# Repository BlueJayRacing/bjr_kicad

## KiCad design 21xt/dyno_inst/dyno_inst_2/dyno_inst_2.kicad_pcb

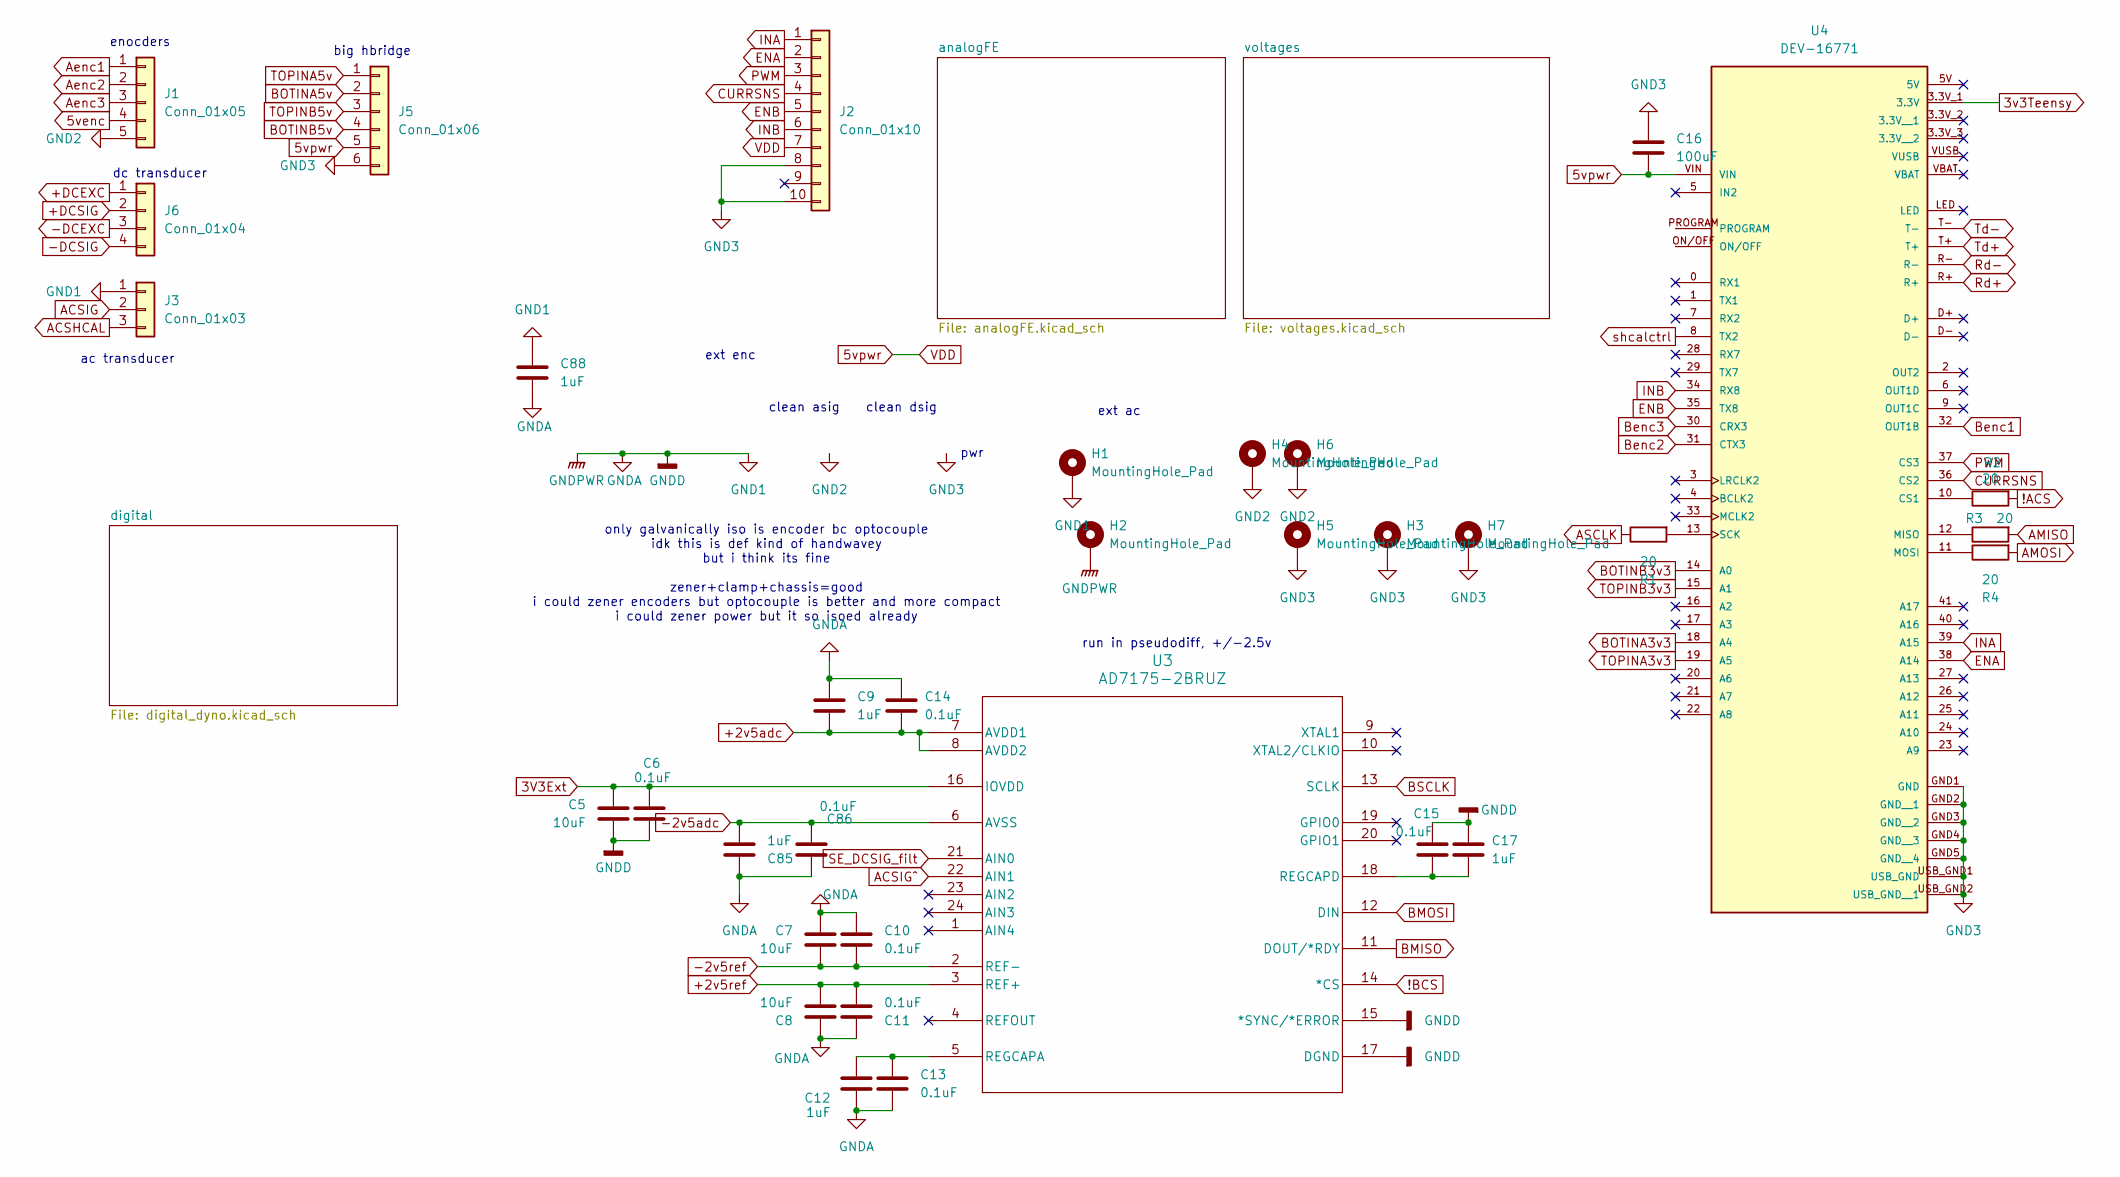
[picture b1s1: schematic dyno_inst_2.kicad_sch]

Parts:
C5, C7, C8: 10uF; C_0402_1005Metric
C6, C10, C11, C13, C14, C15, C86: 0.1uF; C_0402_1005Metric
C9, C12, C17, C85: 1uF; C_0402_1005Metric
C16: 100uF; C_0603_1608Metric
C88: 1uF; C_0603_1608Metric
H1, H2, H3, H4, H5, H6, H7: MountingHole_Pad; MountingHole_3mm_Pad
J1: Conn_01x05; PinHeader_1x05_P2.54mm_Vertical
J2: Conn_01x10; PinHeader_1x10_P2.54mm_Vertical
J3: Conn_01x03; CONN_T4041017041-000_TEC
J5: Conn_01x06; PinHeader_1x06_P2.54mm_Vertical
J6: Conn_01x04; CONN_T4041017041-000_TEC
R1, R2, R3, R4: 20; R_0402_1005Metric
U3: AD7175-2BRUZ; RU_24_ADI
U4: DEV-16771; MODULE_DEV-16771; PARTREV 4.1

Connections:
3V3Ext: C5.1, C6.1, U3.16 (IOVDD)
3v3Teensy: U4.3.3V_1 (3.3V); also elsewhere on the board
5venc: J1.4; also elsewhere on the board
5vpwr: C16.2, J2.7, J5.5, U4.VIN; also elsewhere on the board
!ACS: R2.2; also elsewhere on the board
!BCS: U3.14 (*CS); also elsewhere on the board
+2v5adc: C9.2, C14.2, U3.7 (AVDD1), U3.8 (AVDD2); also elsewhere on the board
+2v5ref: C8.2, C11.2, U3.3 (REF+); also elsewhere on the board
+5vexc: J6.1; also elsewhere on the board
+DCSIG: J6.2; also elsewhere on the board
-2v5adc: C85.2, C86.2, U3.6 (AVSS); also elsewhere on the board
-2v5ref: C7.2, C10.2, U3.2 (REF-); also elsewhere on the board
-5vexc: J6.3; also elsewhere on the board
-DCSIG: J6.4; also elsewhere on the board
ACSHCAL: J3.3; also elsewhere on the board
ACSIG: J3.2; also elsewhere on the board
ACSIG^: U3.22 (AIN1); also elsewhere on the board
AMISO: R3.2; also elsewhere on the board
AMOSI: R4.2; also elsewhere on the board
ASCLK: R1.1; also elsewhere on the board
Aenc1: J1.1; also elsewhere on the board
Aenc2: J1.2; also elsewhere on the board
Aenc3: J1.3; also elsewhere on the board
BMISO: U3.11 (DOUT/*RDY); also elsewhere on the board
BMOSI: U3.12 (DIN); also elsewhere on the board
BOTINA3v3: U4.18 (A4); also elsewhere on the board
BOTINA5v: J5.2; also elsewhere on the board
BOTINB3v3: U4.14 (A0); also elsewhere on the board
BOTINB5v: J5.4; also elsewhere on the board
BSCLK: U3.13 (SCLK); also elsewhere on the board
Benc1: U4.32 (OUT1B); also elsewhere on the board
Benc2: U4.31 (CTX3); also elsewhere on the board
Benc3: U4.30 (CRX3); also elsewhere on the board
CURRSNS: J2.4, U4.36 (CS2)
ENA: J2.2, U4.38 (A14)
ENB: J2.5, U4.35 (TX8)
GND1: C5.2, C6.2, C7.1, C8.1, C9.1, C10.1, C11.1, C12.2, C13.2, C14.1, C15.1, C17.1, C85.1, C86.1, C88.1, C88.2, H1.1, H2.1, J3.1, U3.15 (*SYNC/*ERROR), U3.17 (DGND); also elsewhere on the board
GND2: H4.1, H6.1, J1.5; also elsewhere on the board
GND3: C16.1, H3.1, H5.1, H7.1, J2.8, J2.10, J5.6, U4.GND1 (GND), U4.GND2 (GND__1), U4.GND3 (GND__2), U4.GND4 (GND__3), U4.GND5 (GND__4), U4.USB_GND1 (USB_GND), U4.USB_GND2 (USB_GND__1); also elsewhere on the board
INA: J2.1, U4.39 (A15)
INB: J2.6, U4.34 (RX8)
unnamed: C12.1, C13.1, U3.5 (REGCAPA)
unnamed: C15.2, C17.2, U3.18 (REGCAPD)
unnamed: R2.1, U4.10 (CS1)
unnamed: R3.1, U4.12 (MISO)
unnamed: R4.1, U4.11 (MOSI)
unnamed: R1.2, U4.13 (SCK)
PWM: J2.3, U4.37 (CS3)
Rd+: U4.R+; also elsewhere on the board
Rd-: U4.R-; also elsewhere on the board
SE_DCSIG_filt: U3.21 (AIN0); also elsewhere on the board
TOPINA3v3: U4.19 (A5); also elsewhere on the board
TOPINA5v: J5.1; also elsewhere on the board
TOPINB3v3: U4.15 (A1); also elsewhere on the board
TOPINB5v: J5.3; also elsewhere on the board
Td+: U4.T+; also elsewhere on the board
Td-: U4.T-; also elsewhere on the board
shcalctrl: U4.8 (TX2); also elsewhere on the board

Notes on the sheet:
dc transducer
clean dsig
big hbridge
pwr
ext enc
only galvanically iso is encoder bc optocouple idk this is def kind of handwavey but i think its fine zener+clamp+chassis=good i could zener encoders but optocouple is better and more compact i could zener power but it so isoed already
run in pseudodiff, +/-2.5v
ext ac
clean asig
enocders
ac transducer

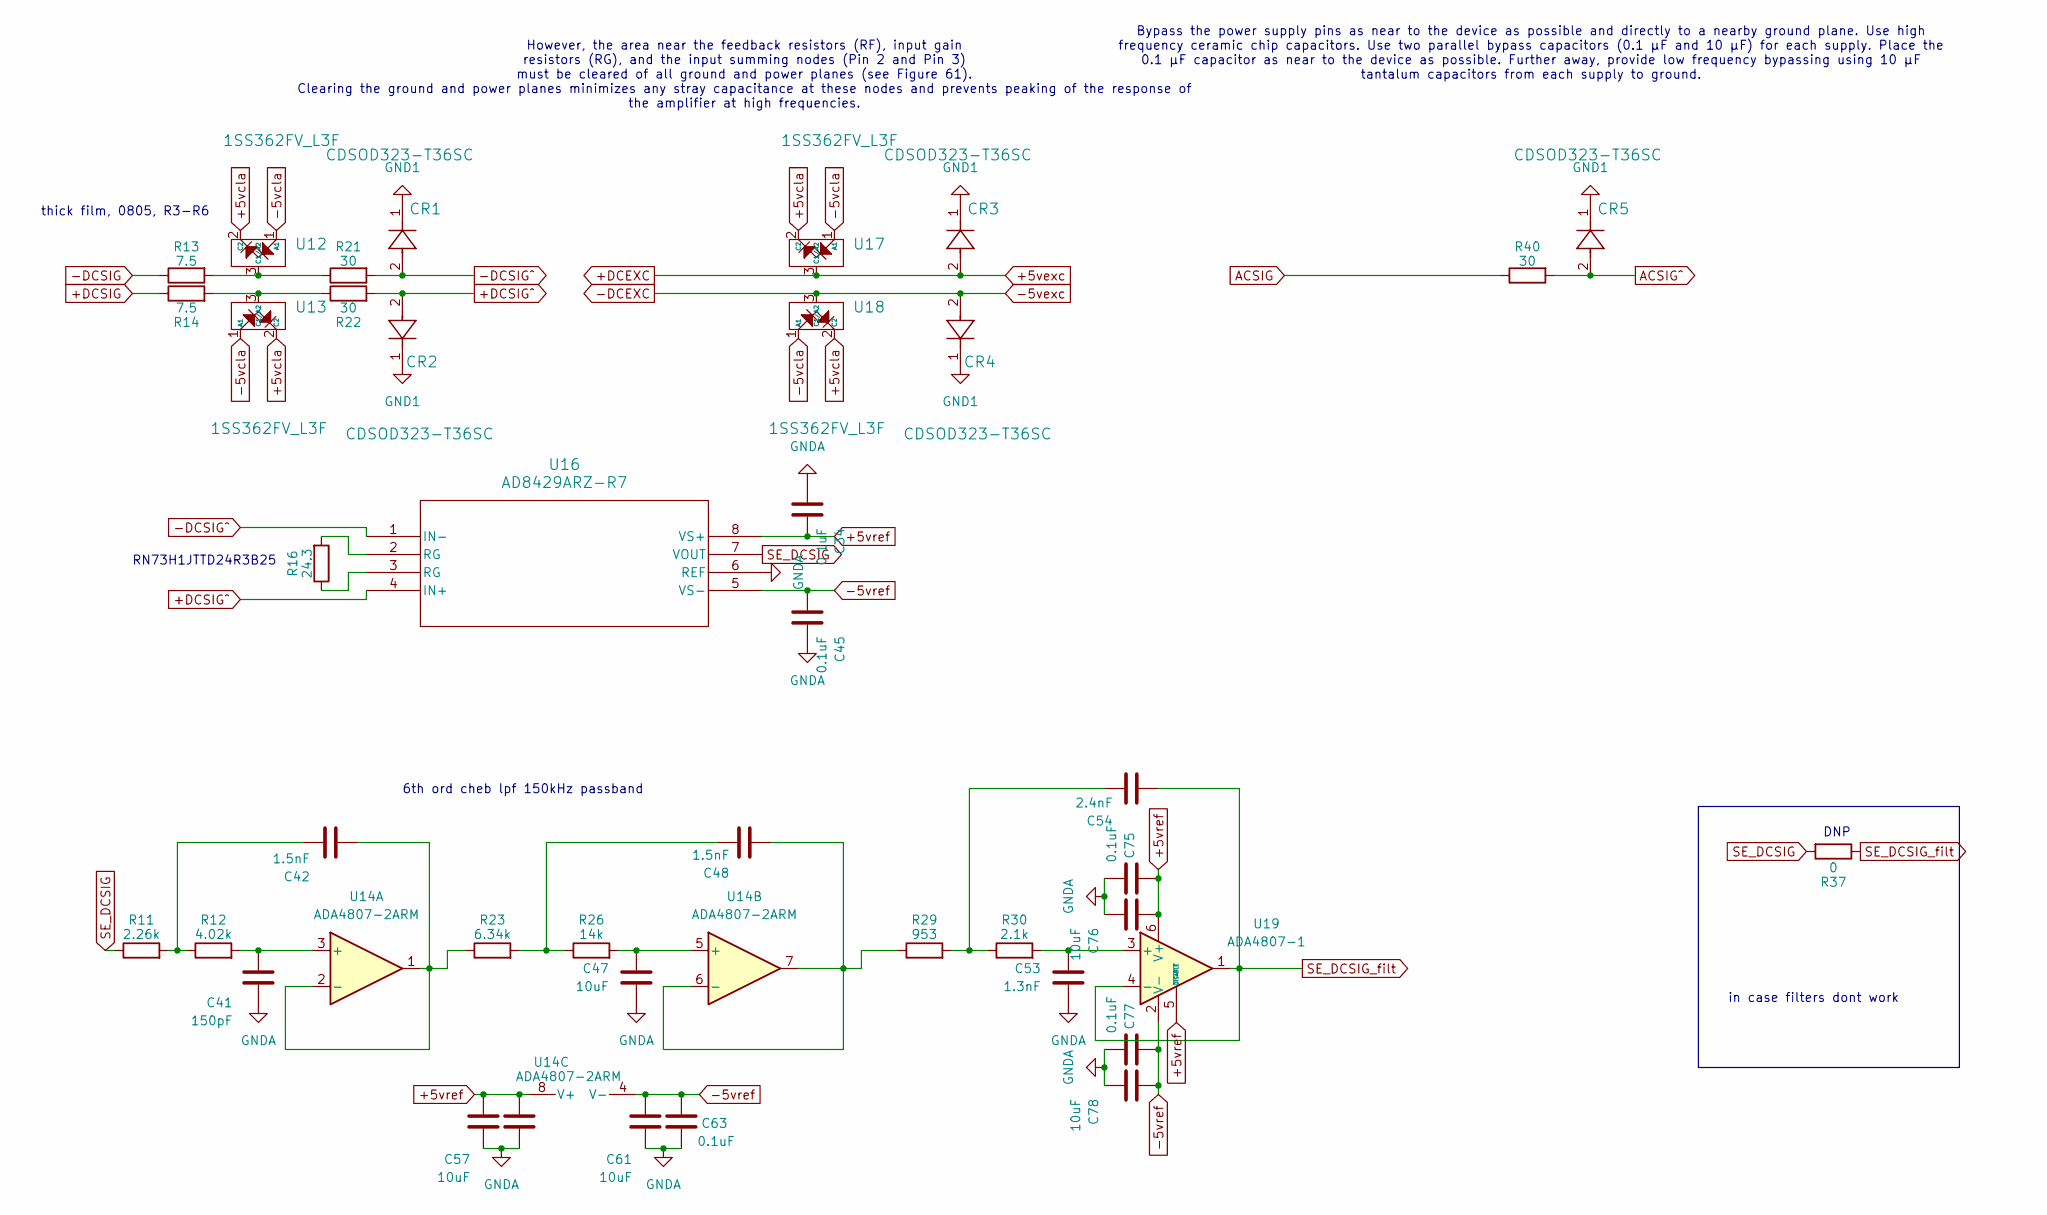
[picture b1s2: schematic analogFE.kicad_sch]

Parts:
C34, C45, C58, C63, C75, C77: 0.1uF; C_0402_1005Metric
C41: 150pF; C_0402_1005Metric
C42, C48: 1.5nF; C_0402_1005Metric
C47, C57, C61, C76, C78: 10uF; C_0402_1005Metric
C53: 1.3nF; C_0402_1005Metric
C54: 2.4nF; C_0402_1005Metric
CR1, CR2, CR3, CR4, CR5: CDSOD323-T36SC; DIODE_CDSOD323-T36SC_BRN
R11: 2.26k; R_0402_1005Metric
R12: 4.02k; R_0402_1005Metric
R13, R14: 7.5; R_0805_2012Metric
R16: 24.3; R_0805_2012Metric
R21, R22, R40: 30; R_0805_2012Metric
R23: 6.34k; R_0402_1005Metric
R26: 14k; R_0402_1005Metric
R29: 953; R_0402_1005Metric
R30: 2.1k; R_0402_1005Metric
R37: 0; R_0402_1005Metric
U12, U13, U17, U18: 1SS362FV_L3F; SOT-723
U14: ADA4807-2ARM; MSOP-8_3x3mm_P0.65mm
U16: AD8429ARZ-R7; R_8_ADI
U19: ADA4807-1; KS-6_ADI

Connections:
+5vcla: U12.2 (C2), U13.2 (C2), U17.2 (C2), U18.2 (C2); also elsewhere on the board
+5vexc: CR3.2, U17.3 (C1/A2); also elsewhere on the board
+5vref: C34.1, C57.1, C58.1, C75.1, C76.1, U14.8 (V+), U16.8 (VS+), U19.5 (~DISABLE), U19.6 (V+); also elsewhere on the board
+DCSIG: R14.1; also elsewhere on the board
+DCSIG^: CR2.2, R22.2, U16.4 (IN+)
-5vcla: U12.1 (A1), U13.1 (A1), U17.1 (A1), U18.1 (A1); also elsewhere on the board
-5vexc: CR4.2, U18.3 (C1/A2); also elsewhere on the board
-5vref: C45.2, C61.1, C63.1, C77.1, C78.1, U14.4 (V-), U16.5 (VS-), U19.2 (V-); also elsewhere on the board
-DCSIG: R13.1; also elsewhere on the board
-DCSIG^: CR1.2, R21.2, U16.1 (IN-)
ACSIG: R40.1; also elsewhere on the board
ACSIG^: CR5.2, R40.2; also elsewhere on the board
GND1: C34.2, C41.2, C45.1, C47.2, C53.2, C57.2, C58.2, C61.2, C63.2, C75.2, C76.2, C77.2, C78.2, CR1.1, CR2.1, CR3.1, CR4.1, CR5.1, U16.6 (REF); also elsewhere on the board
unnamed: C42.1, R11.2, R12.1
unnamed: C48.1, R23.2, R26.1
unnamed: C54.1, R29.2, R30.1
unnamed: R16.1, U16.3 (RG)
unnamed: R16.2, U16.2 (RG)
unnamed: R13.2, R21.1, U12.3 (C1/A2)
unnamed: R14.2, R22.1, U13.3 (C1/A2)
unnamed: C41.1, R12.2, U14.3 (+)
unnamed: C42.2, R23.1, U14.1, U14.2 (-)
unnamed: C47.1, R26.2, U14.5 (+)
unnamed: C48.2, R29.1, U14.6 (-), U14.7
unnamed: C53.1, R30.2, U19.3 (+)
SE_DCSIG: R11.1, R37.2, U16.7 (VOUT)
SE_DCSIG_filt: C54.2, R37.1, U19.1, U19.4 (-); also elsewhere on the board

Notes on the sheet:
in case filters dont work
RN73H1JTTD24R3B25
DNP
6th ord cheb lpf 150kHz passband
However, the area near the feedback resistors (RF), input gain resistors (RG), and the input summing nodes (Pin 2 and Pin 3) must be cleared of all ground and power planes (see Figure 61). Clearing the ground and power planes minimizes any stray capacitance at these nodes and prevents peaking of th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
Bypass the power supply pins as near to the device as possible and directly to a nearby ground plane. Use high frequency ceramic chip capacitors. Use two parallel bypass capacitors (0.1 µF and 10 µF) for each supply. Place the 0.1 µF capacitor as near to the device as possible. Further away, provid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
thick film, 0805, R3-R6

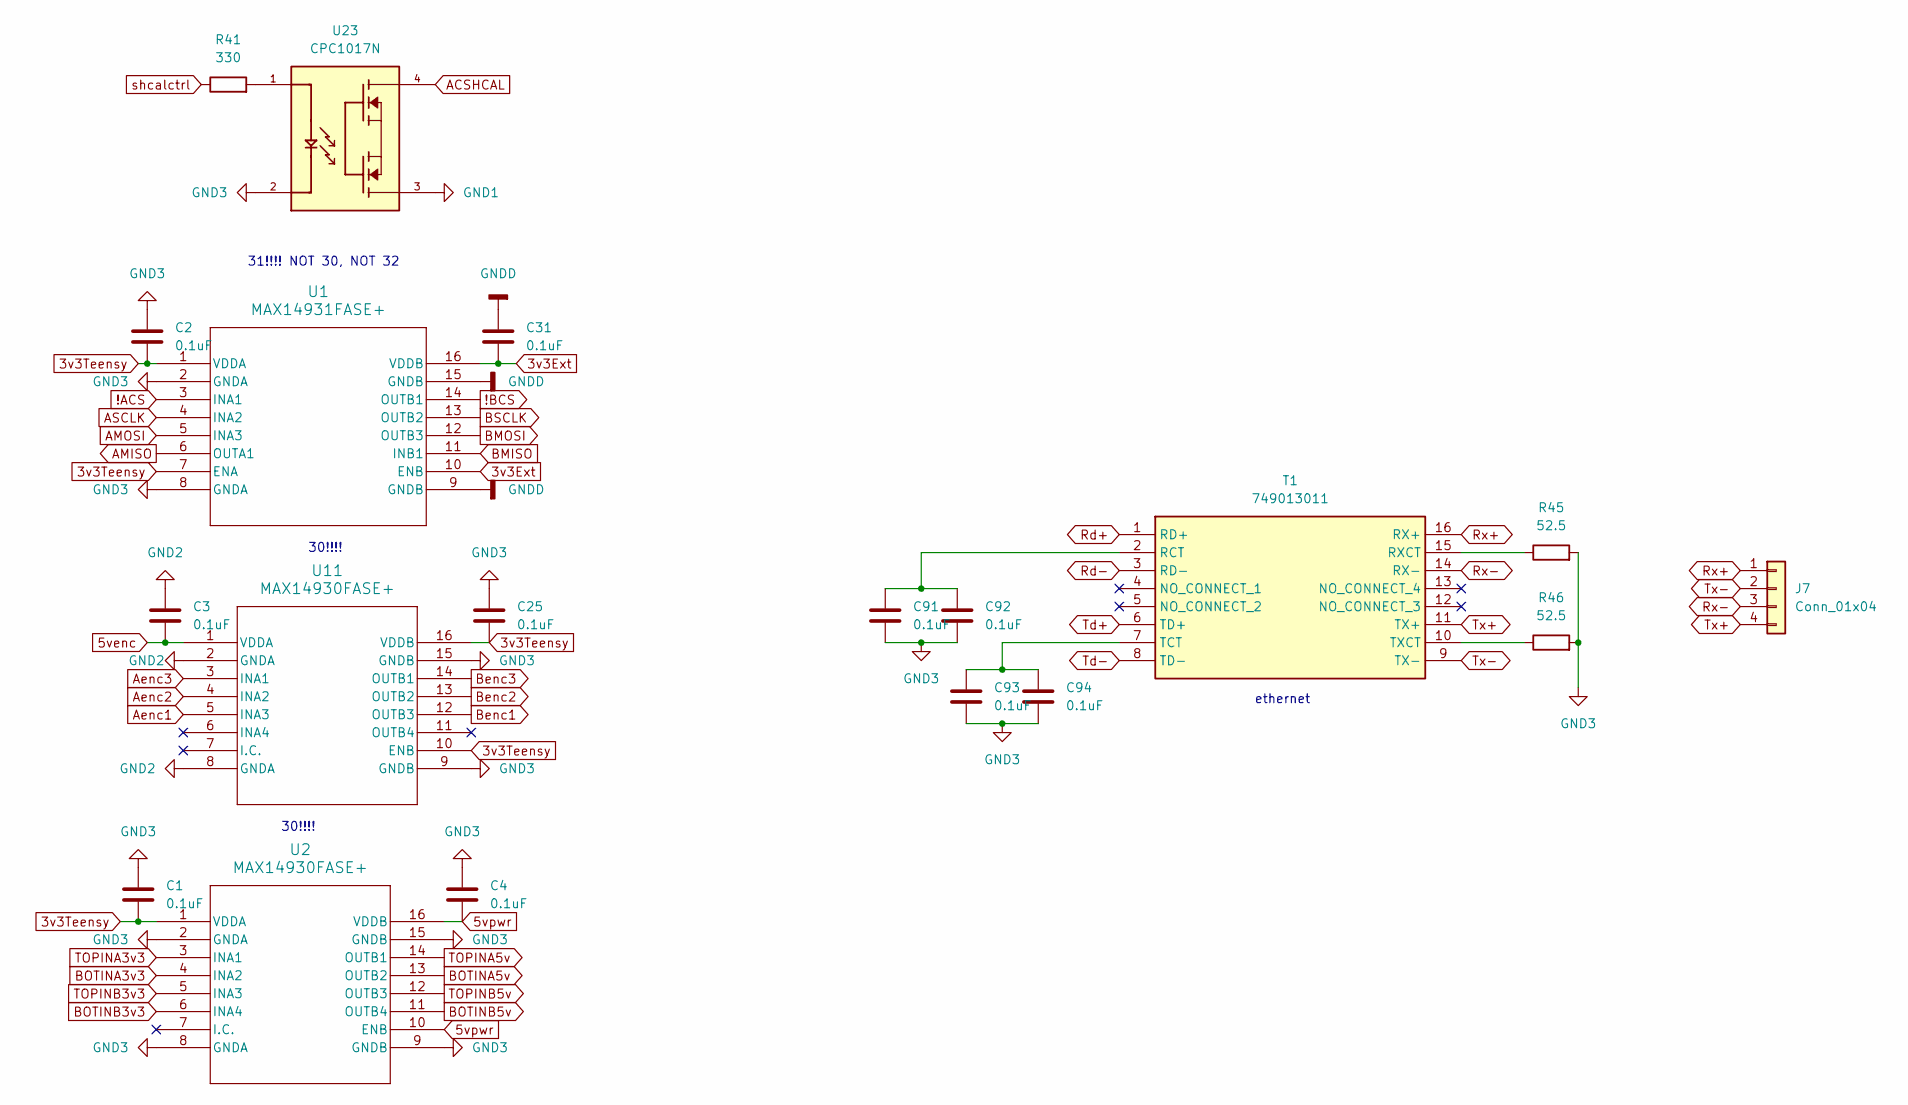
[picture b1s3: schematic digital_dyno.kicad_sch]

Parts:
C1, C2, C3, C4, C25, C31, C91, C92, C93, C94: 0.1uF; C_0402_1005Metric
J7: Conn_01x04; CONN_T4041017041-000_TEC
R41: 330; R_0402_1005Metric
R45, R46: 52.5; R_0402_1005Metric
T1: 749013011; Mouser Part Number 710-749013011
U1: MAX14931FASE+; 21-0041_S16&plus_1_MXM_1
U2, U11: MAX14930FASE+; 21-0041_S16&plus_1_MXM
U23: CPC1017N; SOIC254P610X218-4N

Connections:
3v3Ext: C31.2, U1.10 (ENB), U1.16 (VDDB); also elsewhere on the board
3v3Teensy: C1.2, C2.2, C25.2, U1.1 (VDDA), U1.7 (ENA), U2.1 (VDDA), U11.10 (ENB), U11.16 (VDDB); also elsewhere on the board
5venc: C3.2, U11.1 (VDDA); also elsewhere on the board
5vpwr: C4.2, U2.10 (ENB), U2.16 (VDDB); also elsewhere on the board
!ACS: U1.3 (INA1); also elsewhere on the board
!BCS: U1.14 (OUTB1); also elsewhere on the board
ACSHCAL: U23.4; also elsewhere on the board
AMISO: U1.6 (OUTA1); also elsewhere on the board
AMOSI: U1.5 (INA3); also elsewhere on the board
ASCLK: U1.4 (INA2); also elsewhere on the board
Aenc1: U11.5 (INA3); also elsewhere on the board
Aenc2: U11.4 (INA2); also elsewhere on the board
Aenc3: U11.3 (INA1); also elsewhere on the board
BMISO: U1.11 (INB1); also elsewhere on the board
BMOSI: U1.12 (OUTB3); also elsewhere on the board
BOTINA3v3: U2.4 (INA2); also elsewhere on the board
BOTINA5v: U2.13 (OUTB2); also elsewhere on the board
BOTINB3v3: U2.6 (INA4); also elsewhere on the board
BOTINB5v: U2.11 (OUTB4); also elsewhere on the board
BSCLK: U1.13 (OUTB2); also elsewhere on the board
Benc1: U11.12 (OUTB3); also elsewhere on the board
Benc2: U11.13 (OUTB2); also elsewhere on the board
Benc3: U11.14 (OUTB1); also elsewhere on the board
GND1: C31.1, U1.9 (GNDB), U1.15 (GNDB), U23.3; also elsewhere on the board
GND2: C3.1, U11.2 (GNDA), U11.8 (GNDA); also elsewhere on the board
GND3: C1.1, C2.1, C4.1, C25.1, C91.2, C92.2, C93.2, C94.2, R45.2, R46.2, U1.2 (GNDA), U1.8 (GNDA), U2.2 (GNDA), U2.8 (GNDA), U2.9 (GNDB), U2.15 (GNDB), U11.9 (GNDB), U11.15 (GNDB), U23.2; also elsewhere on the board
unnamed: R41.2, U23.1
unnamed: C91.1, C92.1, T1.2 (RCT)
unnamed: R45.1, T1.15 (RXCT)
unnamed: C93.1, C94.1, T1.7 (TCT)
unnamed: R46.1, T1.10 (TXCT)
Rd+: T1.1 (RD+); also elsewhere on the board
Rd-: T1.3 (RD-); also elsewhere on the board
Rx+: J7.1, T1.16 (RX+)
Rx-: J7.3, T1.14 (RX-)
TOPINA3v3: U2.3 (INA1); also elsewhere on the board
TOPINA5v: U2.14 (OUTB1); also elsewhere on the board
TOPINB3v3: U2.5 (INA3); also elsewhere on the board
TOPINB5v: U2.12 (OUTB3); also elsewhere on the board
Td+: T1.6 (TD+); also elsewhere on the board
Td-: T1.8 (TD-); also elsewhere on the board
Tx+: J7.4, T1.11 (TX+)
Tx-: J7.2, T1.9 (TX-)
shcalctrl: R41.1; also elsewhere on the board

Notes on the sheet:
31!!!! NOT 30, NOT 32
30!!!!
ethernet

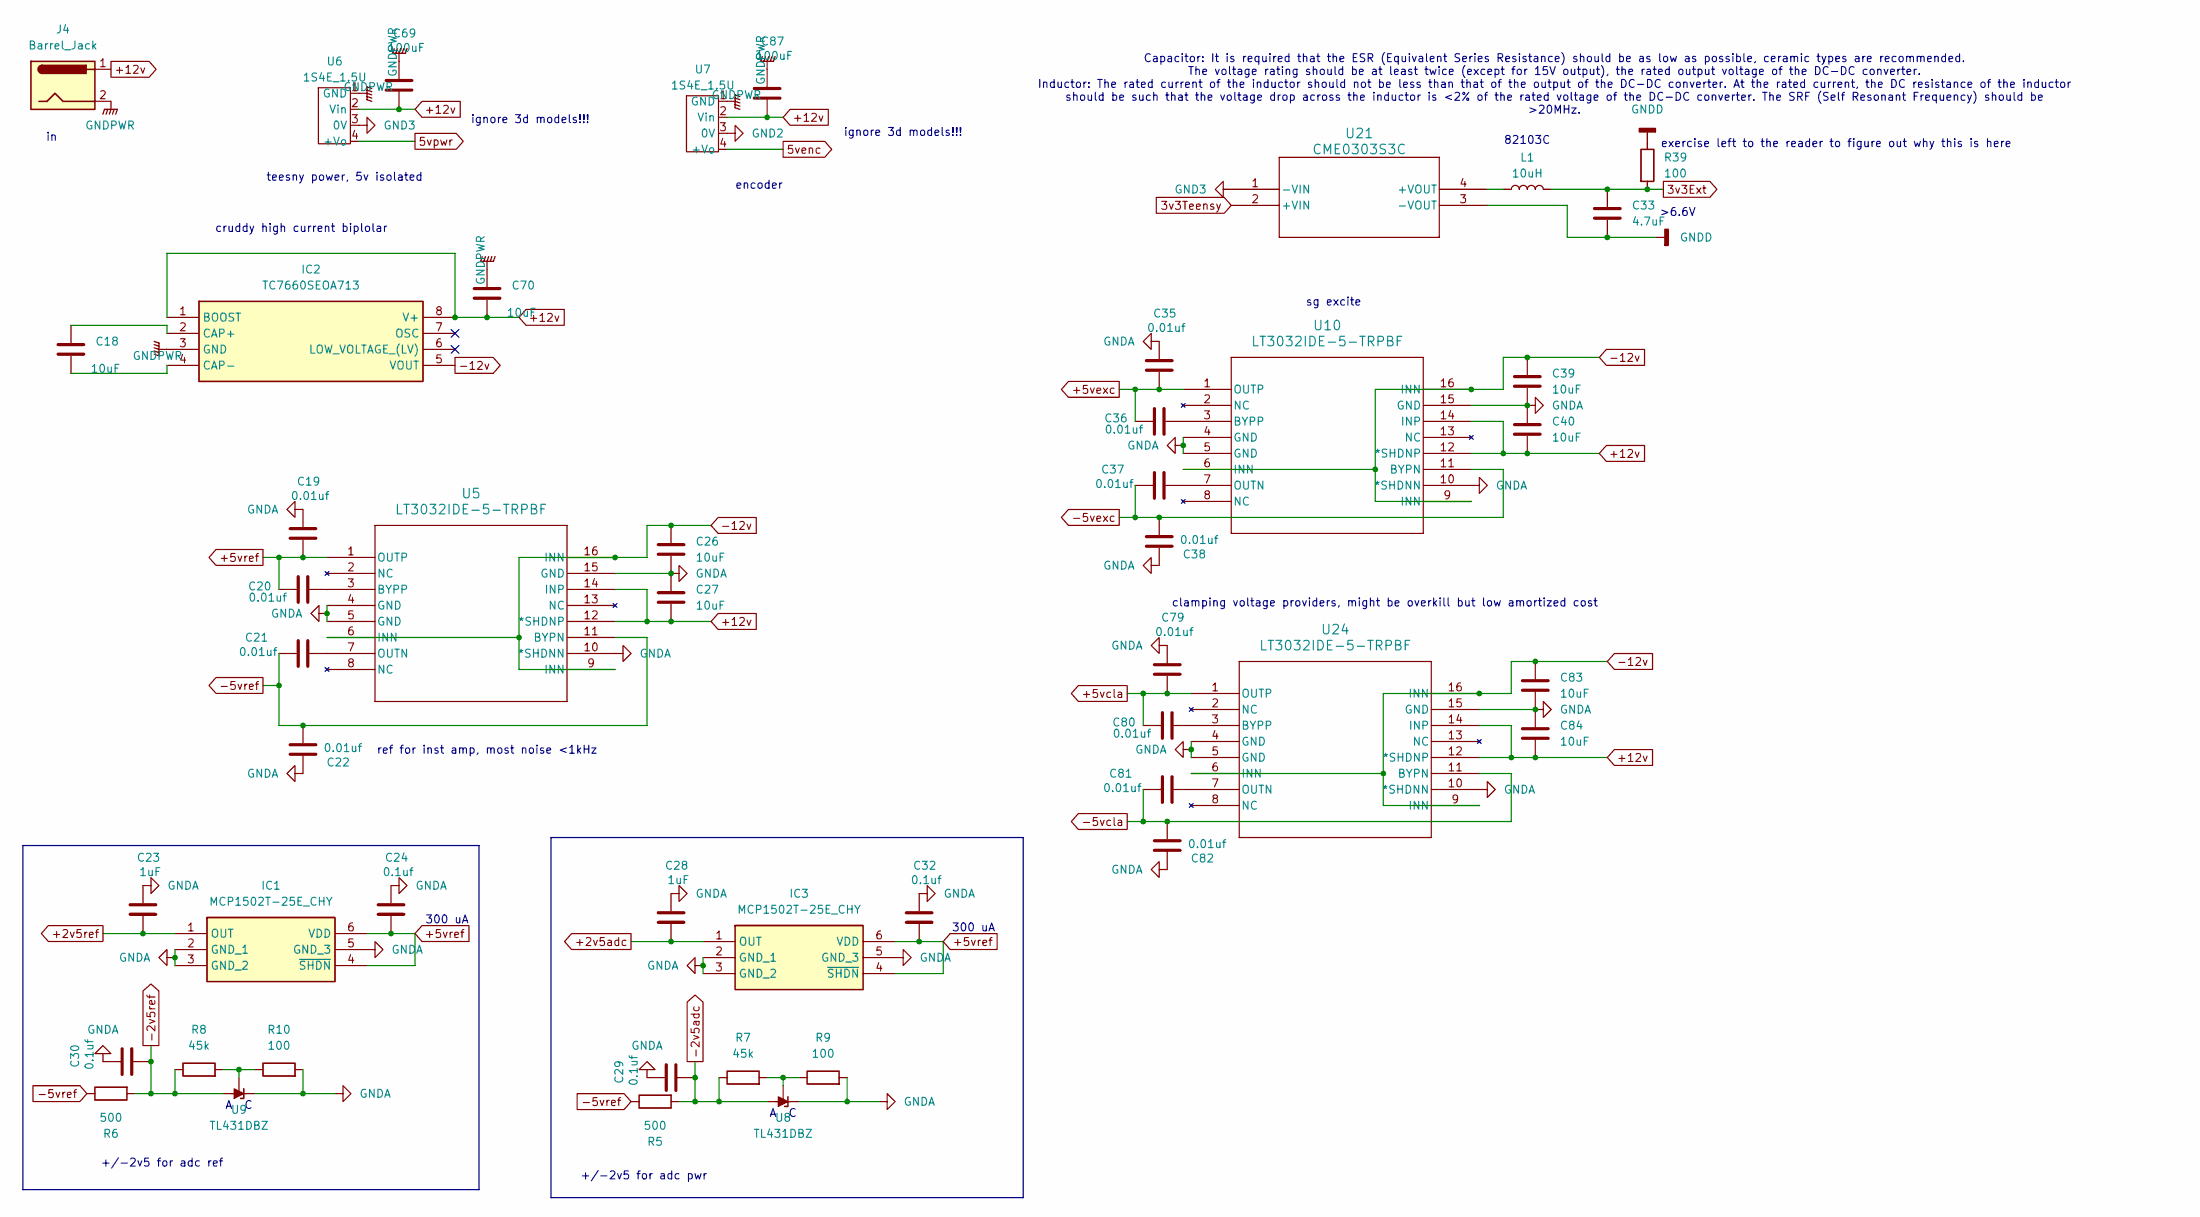
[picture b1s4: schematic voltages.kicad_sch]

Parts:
C18, C70: 10uF; C_0603_1608Metric
C19, C20, C21, C22, C35, C36, C37, C38, C79, C80, C81, C82: 0.01uf; C_0402_1005Metric
C23, C28: 1uF; C_0402_1005Metric
C24, C29, C30, C32: 0.1uf; C_0402_1005Metric
C26, C27, C39, C40, C83, C84: 10uF; C_0402_1005Metric
C33: 4.7uF; C_0402_1005Metric
C69, C87: 100uF; C_0805_2012Metric
IC1, IC3: MCP1502T-25E_CHY; SOT95P280X145-6N; Mouser Part Number 579-MCP1502T-50E/CHY
IC2: TC7660SEOA713; SOIC127P600X175-8N; Mouser Part Number 579-TC7660SEOA713
J4: Barrel_Jack; CUI_PJ-037A
L1: 10uH; L_1210_3225Metric
R5, R6: 500; R_0402_1005Metric
R7, R8: 45k; R_0402_1005Metric
R9, R10, R39: 100; R_0402_1005Metric
U5, U10, U24: LT3032IDE-5-TRPBF; DFN14_DE14MA_ADI
U6, U7: 1S4E_1.5U; PinHeader_1x04_P2.54mm_Vertical
U8, U9: TL431DBZ; SOT-23
U21: CME0303S3C; SIP4_CME0303_MUR

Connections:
3v3Ext: C33.1, L1.2, R39.2; also elsewhere on the board
3v3Teensy: U21.2 (+VIN); also elsewhere on the board
5venc: U7.4 (+Vo); also elsewhere on the board
5vpwr: U6.4 (+Vo); also elsewhere on the board
+2v5adc: C28.2, IC3.1 (OUT); also elsewhere on the board
+2v5ref: C23.2, IC1.1 (OUT); also elsewhere on the board
+5vcla: C79.2, C80.1, U24.1 (OUTP); also elsewhere on the board
+5vexc: C35.2, C36.1, U10.1 (OUTP); also elsewhere on the board
+5vref: C19.2, C20.1, C24.2, C32.2, IC1.4 (~SHDN), IC1.6 (VDD), IC3.4 (~SHDN), IC3.6 (VDD), U5.1 (OUTP); also elsewhere on the board
+12v: C27.2, C40.2, C69.2, C70.2, C84.2, C87.2, IC2.1 (BOOST), IC2.8 (V+), J4.1, U5.12 (*SHDNP), U5.14 (INP), U6.2 (Vin), U7.2 (Vin), U10.12 (*SHDNP), U10.14 (INP), U24.12 (*SHDNP), U24.14 (INP)
-2v5adc: C29.2, R5.2, R7.1, U8.3 (A); also elsewhere on the board
-2v5ref: C30.2, R6.2, R8.1, U9.3 (A); also elsewhere on the board
-5vcla: C81.1, C82.2, U24.11 (BYPN); also elsewhere on the board
-5vexc: C37.1, C38.2, U10.11 (BYPN); also elsewhere on the board
-5vref: C21.1, C22.2, R5.1, R6.1, U5.11 (BYPN); also elsewhere on the board
-12v: C26.1, C39.1, C83.1, IC2.5 (VOUT), U5.6 (INN), U5.9 (INN), U5.16 (INN), U10.6 (INN), U10.9 (INN), U10.16 (INN), U24.6 (INN), U24.9 (INN), U24.16 (INN)
GND1: C19.1, C22.1, C23.1, C24.1, C26.2, C27.1, C28.1, C29.1, C30.1, C32.1, C33.2, C35.1, C38.1, C39.2, C40.1, C69.1, C70.1, C79.1, C82.1, C83.2, C84.1, C87.1, IC1.2 (GND_1), IC1.3 (GND_2), IC1.5 (GND_3), IC2.3 (GND), IC3.2 (GND_1), IC3.3 (GND_2), IC3.5 (GND_3), J4.2, R9.2, R10.2, R39.1, U5.4 (GND), U5.5 (GND), U5.10 (*SHDNN), U5.15 (GND), U6.1 (GND), U7.1 (GND), U8.1 (K), U9.1 (K), U10.4 (GND), U10.5 (GND), U10.10 (*SHDNN), U10.15 (GND), U21.3 (-VOUT), U24.4 (GND), U24.5 (GND), U24.10 (*SHDNN), U24.15 (GND); also elsewhere on the board
GND2: U7.3 (0V); also elsewhere on the board
GND3: U6.3 (0V), U21.1 (-VIN); also elsewhere on the board
unnamed: C18.1, IC2.2 (CAP+)
unnamed: C18.2, IC2.4 (CAP-)
unnamed: C20.2, U5.3 (BYPP)
unnamed: C21.2, U5.7 (OUTN)
unnamed: R7.2, R9.1, U8.2 (REF)
unnamed: R8.2, R10.1, U9.2 (REF)
unnamed: C36.2, U10.3 (BYPP)
unnamed: C37.2, U10.7 (OUTN)
unnamed: L1.1, U21.4 (+VOUT)
unnamed: C80.2, U24.3 (BYPP)
unnamed: C81.2, U24.7 (OUTN)

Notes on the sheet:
cruddy high current biplolar
clamping voltage providers, might be overkill but low amortized cost
exercise left to the reader to figure out why this is here
encoder
Capacitor: It is required that the ESR (Equivalent Series Resistance) should be as low as possible, ceramic types are recommended. The voltage rating should be at least twice (except for 15V output), the rated output voltage of the DC-DC converter. Inductor: The rated current of the inductor should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
ignore 3d models!!!
+/-2v5 for adc pwr
300 uA
+/-2v5 for adc ref
teesny power, 5v isolated
A C
>6.6V
sg excite
ref for inst amp, most noise <1kHz
82103C

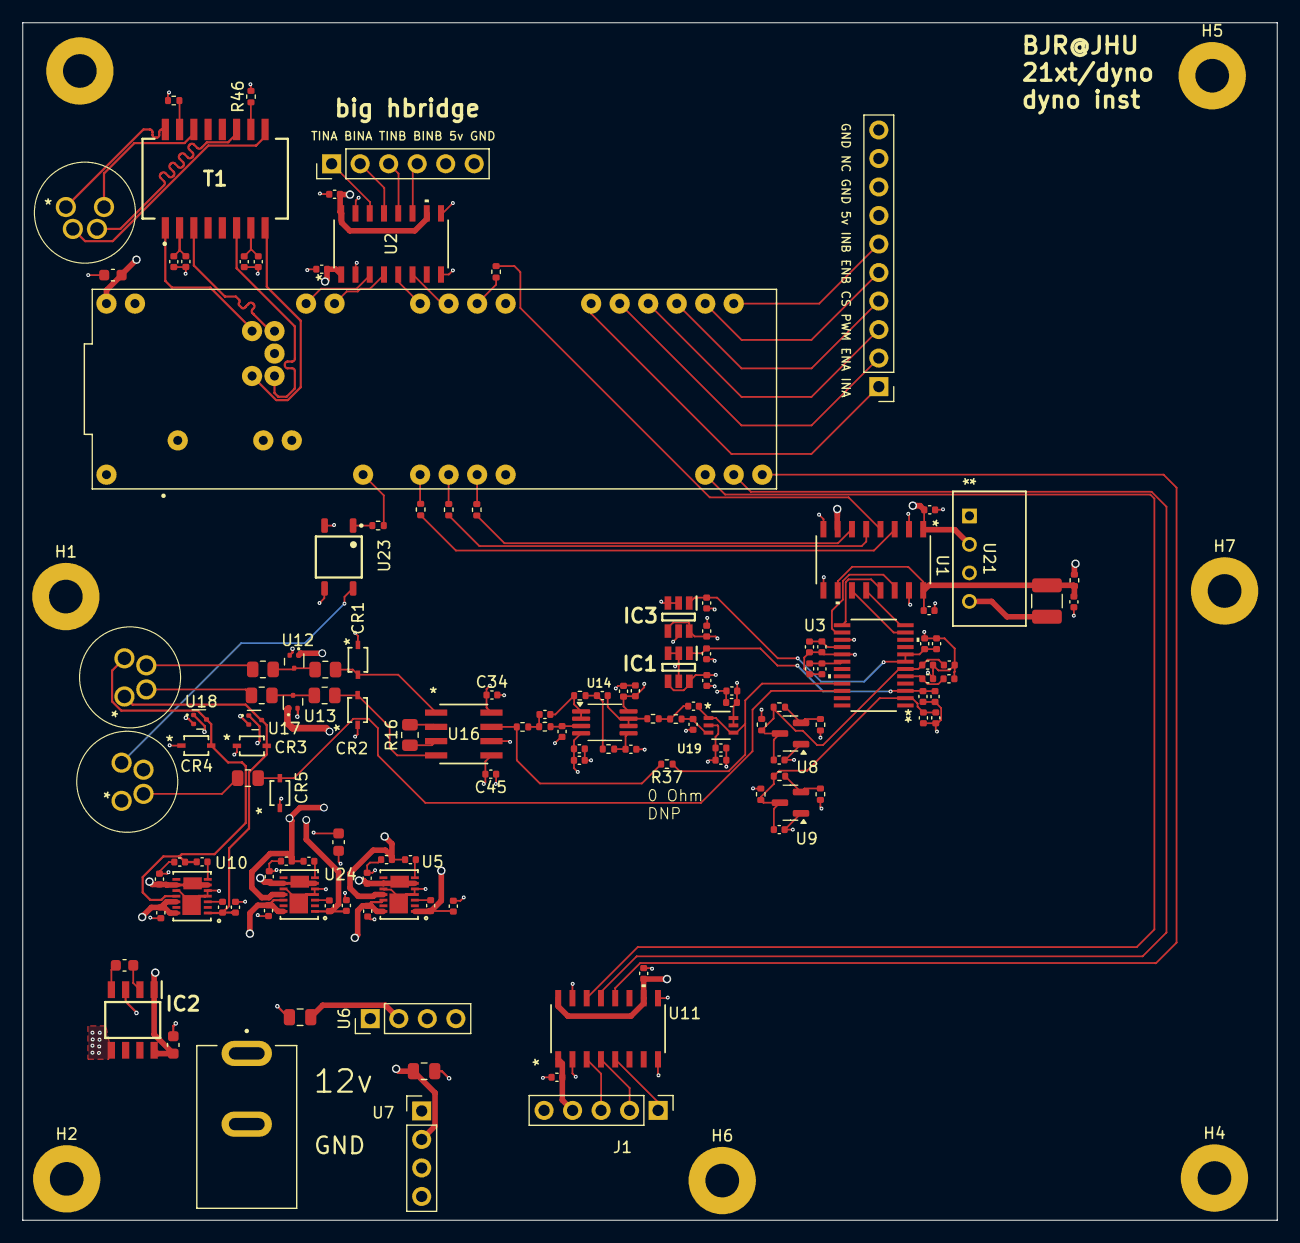
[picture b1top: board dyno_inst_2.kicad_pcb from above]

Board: 4 copper layers, 111.8 x 106.7 mm, 143 parts (0 on the bottom side), 100 nets.

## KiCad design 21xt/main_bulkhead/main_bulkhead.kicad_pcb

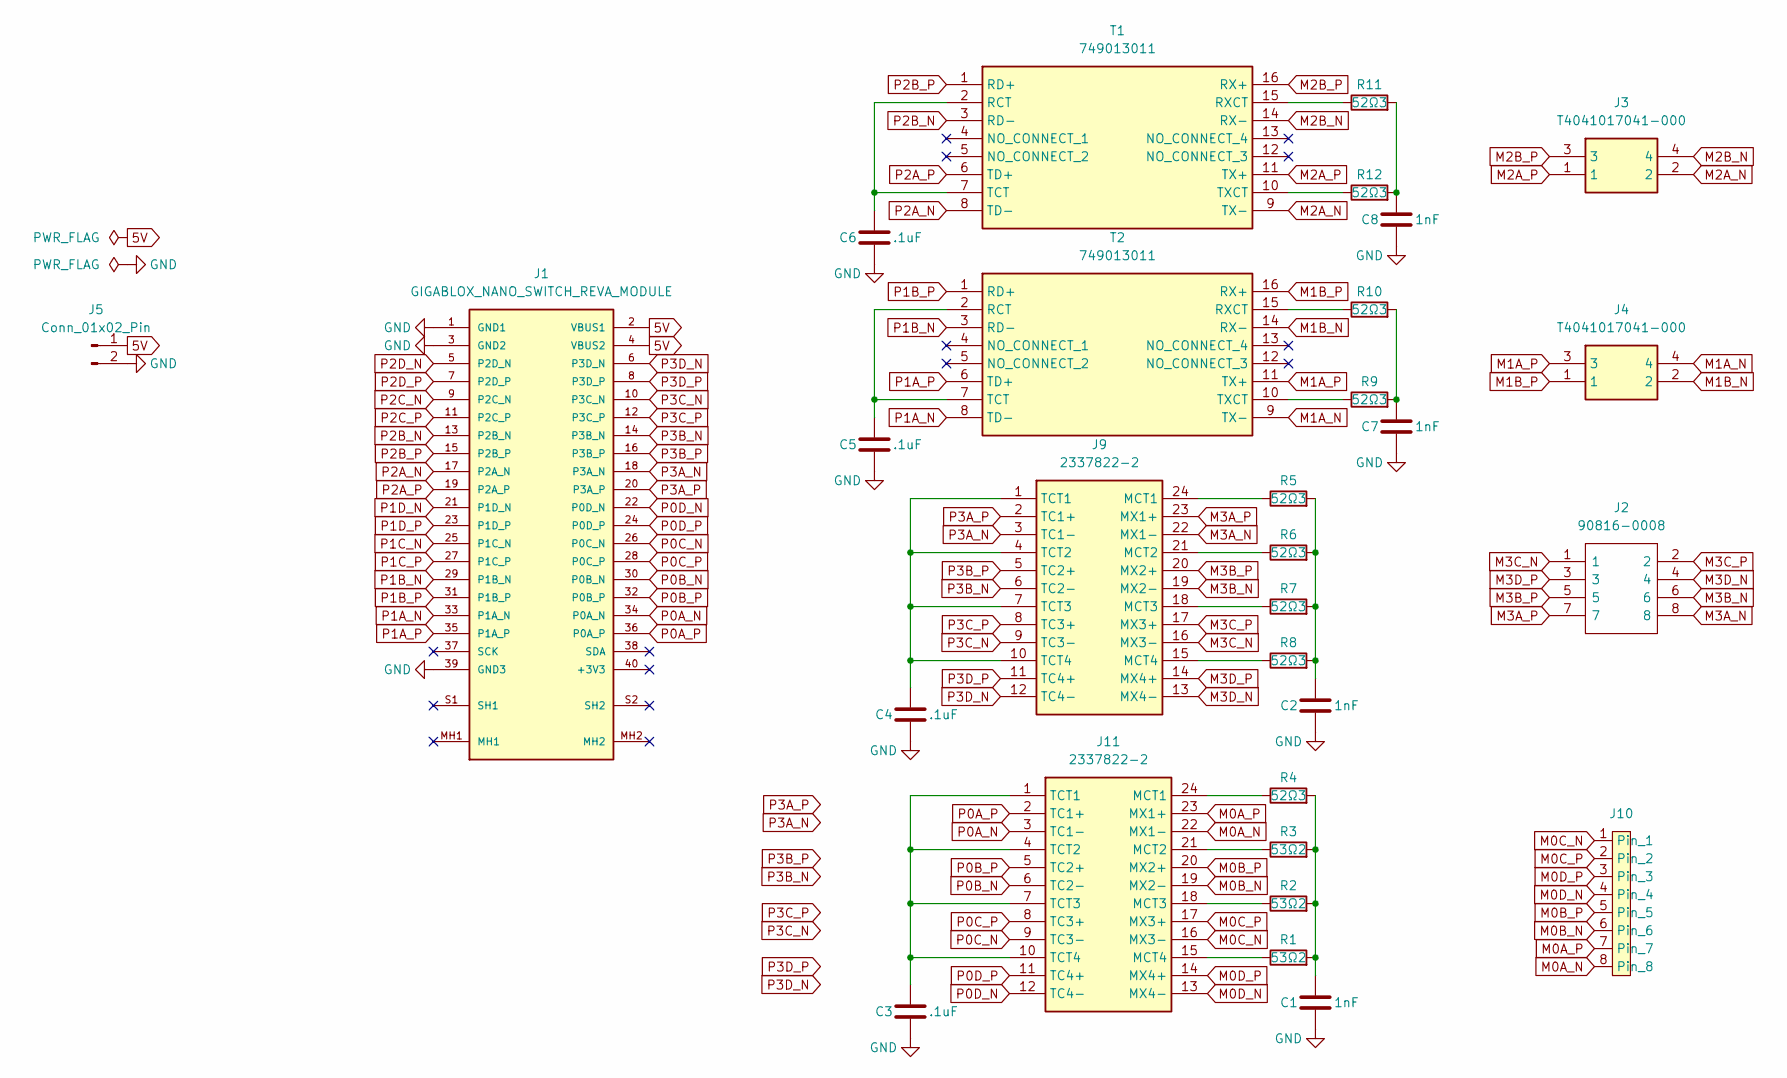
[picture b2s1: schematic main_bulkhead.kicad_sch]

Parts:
C1, C2, C7, C8: 1nF; C_1206_3216Metric
C3, C4, C5, C6: .1uF; C_0402_1005Metric
J1: GIGABLOX_NANO_SWITCH_REVA_MODULE; LSHM-120-02.5-L-DV-A-S-K-TR
J2: 90816-0008; 908160008; Mouser Part Number 538-90816-0008
J3, J4: T4041017041-000; T4041017041000; Mouser Part Number 571-T4041017041-000
J5: Conn_01x02_Pin; JST_PH_B2B-PH-K_1x02_P2.00mm_Vertical
J9, J11: 2337822-2; 23378222; Mouser Part Number 571-2337822-2
J10: m12 8p
R1, R2, R3: 53Ω2; R_0402_1005Metric
R4, R5, R6, R7, R8, R9, R10, R11, R12: 52Ω3; R_0402_1005Metric
T1, T2: 749013011; Mouser Part Number 710-749013011

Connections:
5V: J1.2 (VBUS1), J1.4 (VBUS2), J5.1
GND: C1.2, C2.2, C3.2, C4.2, C5.2, C6.2, C7.2, C8.2, J1.1 (GND1), J1.3 (GND2), J1.39 (GND3), J5.2
M0A_N: J10.8, J11.22 (MX1-)
M0A_P: J10.7, J11.23 (MX1+)
M0B_N: J10.6, J11.19 (MX2-)
M0B_P: J10.5, J11.20 (MX2+)
M0C_N: J10.1, J11.16 (MX3-)
M0C_P: J10.2, J11.17 (MX3+)
M0D_N: J10.4, J11.13 (MX4-)
M0D_P: J10.3, J11.14 (MX4+)
M1A_N: J4.4, T2.9 (TX-)
M1A_P: J4.3, T2.11 (TX+)
M1B_N: J4.2, T2.14 (RX-)
M1B_P: J4.1, T2.16 (RX+)
M2A_N: J3.2, T1.9 (TX-)
M2A_P: J3.1, T1.11 (TX+)
M2B_N: J3.4, T1.14 (RX-)
M2B_P: J3.3, T1.16 (RX+)
M3A_N: J2.8, J9.22 (MX1-)
M3A_P: J2.7, J9.23 (MX1+)
M3B_N: J2.6, J9.19 (MX2-)
M3B_P: J2.5, J9.20 (MX2+)
M3C_N: J2.1, J9.16 (MX3-)
M3C_P: J2.2, J9.17 (MX3+)
M3D_N: J2.4, J9.13 (MX4-)
M3D_P: J2.3, J9.14 (MX4+)
unnamed: C1.1, R1.2, R2.2, R3.2, R4.2
unnamed: C2.1, R5.2, R6.2, R7.2, R8.2
unnamed: C7.1, R9.2, R10.2
unnamed: C8.1, R11.2, R12.2
unnamed: J9.24 (MCT1), R5.1
unnamed: J9.21 (MCT2), R6.1
unnamed: J9.18 (MCT3), R7.1
unnamed: J9.15 (MCT4), R8.1
unnamed: C4.1, J9.1 (TCT1), J9.4 (TCT2), J9.7 (TCT3), J9.10 (TCT4)
unnamed: J11.24 (MCT1), R4.1
unnamed: J11.21 (MCT2), R3.1
unnamed: J11.18 (MCT3), R2.1
unnamed: J11.15 (MCT4), R1.1
unnamed: C3.1, J11.1 (TCT1), J11.4 (TCT2), J11.7 (TCT3), J11.10 (TCT4)
unnamed: C6.1, T1.2 (RCT), T1.7 (TCT)
unnamed: R11.1, T1.15 (RXCT)
unnamed: R12.1, T1.10 (TXCT)
unnamed: C5.1, T2.2 (RCT), T2.7 (TCT)
unnamed: R10.1, T2.15 (RXCT)
unnamed: R9.1, T2.10 (TXCT)
P0A_N: J1.34 (P0A_N), J11.3 (TC1-)
P0A_P: J1.36 (P0A_P), J11.2 (TC1+)
P0B_N: J1.30 (P0B_N), J11.6 (TC2-)
P0B_P: J1.32 (P0B_P), J11.5 (TC2+)
P0C_N: J1.26 (P0C_N), J11.9 (TC3-)
P0C_P: J1.28 (P0C_P), J11.8 (TC3+)
P0D_N: J1.22 (P0D_N), J11.12 (TC4-)
P0D_P: J1.24 (P0D_P), J11.11 (TC4+)
P1A_N: J1.33 (P1A_N), T2.8 (TD-)
P1A_P: J1.35 (P1A_P), T2.6 (TD+)
P1B_N: J1.29 (P1B_N), T2.3 (RD-)
P1B_P: J1.31 (P1B_P), T2.1 (RD+)
P1C_N: J1.25 (P1C_N)
P1C_P: J1.27 (P1C_P)
P1D_N: J1.21 (P1D_N)
P1D_P: J1.23 (P1D_P)
P2A_N: J1.17 (P2A_N), T1.8 (TD-)
P2A_P: J1.19 (P2A_P), T1.6 (TD+)
P2B_N: J1.13 (P2B_N), T1.3 (RD-)
P2B_P: J1.15 (P2B_P), T1.1 (RD+)
P2C_N: J1.9 (P2C_N)
P2C_P: J1.11 (P2C_P)
P2D_N: J1.5 (P2D_N)
P2D_P: J1.7 (P2D_P)
P3A_N: J1.18 (P3A_N), J9.3 (TC1-)
P3A_P: J1.20 (P3A_P), J9.2 (TC1+)
P3B_N: J1.14 (P3B_N), J9.6 (TC2-)
P3B_P: J1.16 (P3B_P), J9.5 (TC2+)
P3C_N: J1.10 (P3C_N), J9.9 (TC3-)
P3C_P: J1.12 (P3C_P), J9.8 (TC3+)
P3D_N: J1.6 (P3D_N), J9.12 (TC4-)
P3D_P: J1.8 (P3D_P), J9.11 (TC4+)
